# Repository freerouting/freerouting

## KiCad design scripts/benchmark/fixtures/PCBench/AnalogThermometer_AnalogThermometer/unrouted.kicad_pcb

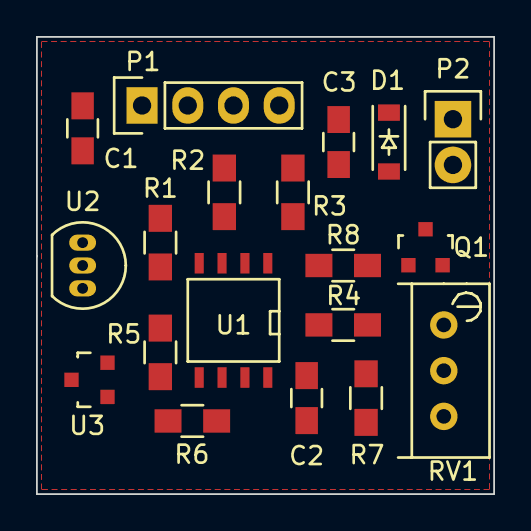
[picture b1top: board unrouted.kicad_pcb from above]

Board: 2 copper layers, 25.4 x 25.4 mm, 19 parts (0 on the bottom side), 12 nets, no tracks yet.

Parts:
C1, C2, C3: 0.1uF; C_0805_HandSoldering
D1: 1N4148; SOD-123
P1: Power; Socket_Strip_Straight_1x04
P2: uA; Socket_Strip_Straight_1x02
Q1: MMBT3904; SOT-23
R1, R4: 1M; R_0805_HandSoldering
R2, R5: 2.2M; R_0805_HandSoldering
R3, R6: 200k; R_0805_HandSoldering
R7: 49.9k; R_0805_HandSoldering
R8: 100; R_0805_HandSoldering
RV1: 100k; Potentiometer_Bourns_3296W_3-8Zoll_Inline_ScrewUp
U1: LTC1541; SOIC-8-N
U2: MCP9700A; TO-92_Inline_Narrow_Oval
U3: MCP9700AT; SOT-23

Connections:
+5V: C1.2, C2.2, C3.2, D1.1, P1.1, P2.1, U1.8, U2.1, U3.1
GND: C1.1, C2.1, P1.4, R3.1, R7.1, RV1.2, RV1.3, U1.4, U1.5, U2.3, U3.3
unnamed: C3.1, D1.2, P2.2, Q1.3
unnamed: Q1.1, R8.1
unnamed: Q1.2, R4.1, R7.2, RV1.1
unnamed: R1.1, R2.2, U1.3
unnamed: R1.2, U2.2, U3.2
unnamed: R2.1, R3.2
unnamed: R4.2, R5.2, U1.2
unnamed: R5.1, R6.2
unnamed: R6.1, U1.6
unnamed: R8.2, U1.1

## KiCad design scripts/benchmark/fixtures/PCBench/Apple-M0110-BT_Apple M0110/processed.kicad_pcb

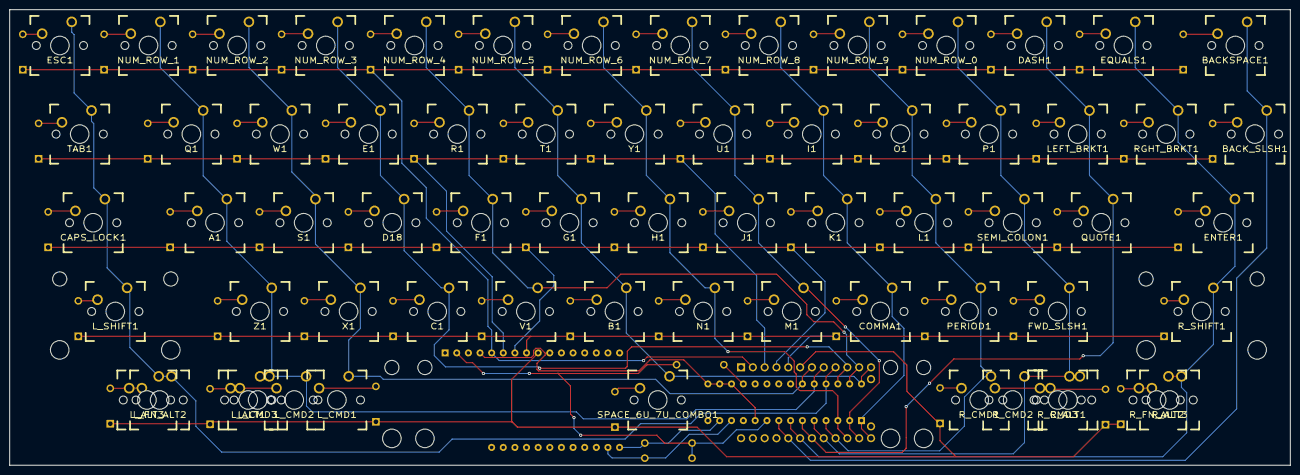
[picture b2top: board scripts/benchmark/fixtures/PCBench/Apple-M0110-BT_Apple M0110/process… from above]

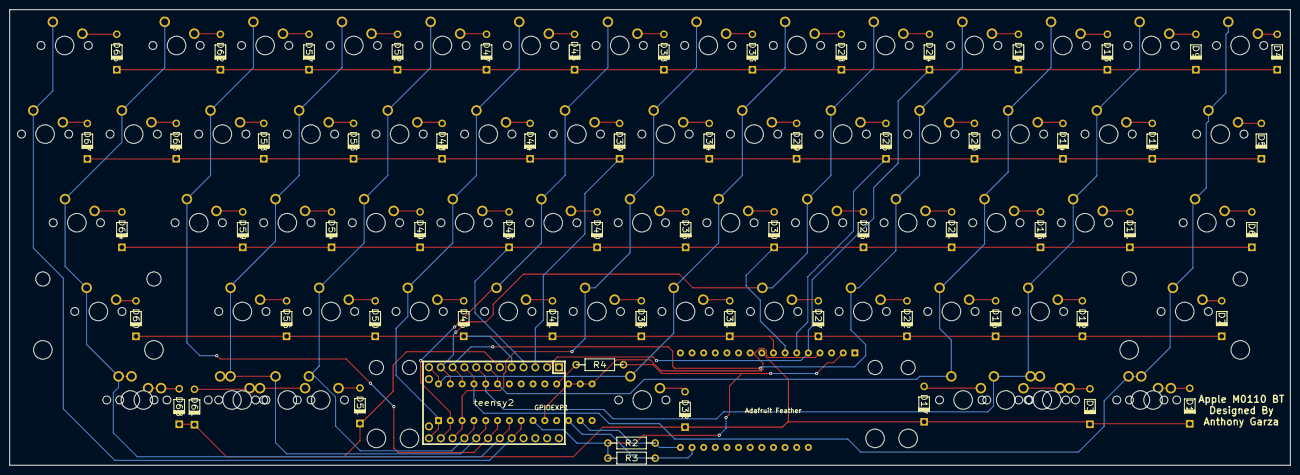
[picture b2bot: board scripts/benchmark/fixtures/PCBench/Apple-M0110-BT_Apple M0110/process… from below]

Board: 2 copper layers, 275.3 x 97.9 mm, 132 parts (66 on the bottom side), 84 nets.

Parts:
A1: SW_PUSH; MX_PCB_100H
Adafruit Feather: Adafruit_Feather; feather_32u4_bluefruit_le
B1: SW_PUSH; MX_PCB_100H
BACKSPACE1: SW_PUSH; MX_PCB_150H
BACK_SLSH1: SW_PUSH; MX_PCB_100H
C1: SW_PUSH; MX_PCB_100H
CAPS_LOCK1: SW_PUSH; MX_PCB_175H
COMMA1: SW_PUSH; MX_PCB_100H
Controller1: teensy2; Teensy_2.0
D1, D3, D4, D5, D6, D7, D9, D10, D11, D12, D13, D14, D15, D16, D17, D19, D20, D21, D22, D24, D25, D26, D27, D28, D29, D30, D31, D32, D33, D34, D35, D36, D38, D39, D40, D41, D43, D44, D45, D46, D47, D48, D49, D50, D51, D52, D53, D54, D55, D57, D58, D59, D60, D61, D62, D63, D64, D66, D67, D68: DIODE; Diode
D18: SW_PUSH; MX_PCB_100H
DASH1: SW_PUSH; MX_PCB_100H
E1: SW_PUSH; MX_PCB_100H
ENTER1: SW_PUSH; MX_PCB_175H
EQUALS1: SW_PUSH; MX_PCB_100H
ESC1: SW_PUSH; MX_PCB_100H
F1: SW_PUSH; MX_PCB_100H
FWD_SLSH1: SW_PUSH; MX_PCB_100H
G1: SW_PUSH; MX_PCB_100H
GPIOEXP1: MCP23017; MCP23017-E-SP-ND
H1: SW_PUSH; MX_PCB_100H
I1: SW_PUSH; MX_PCB_100H
J1: SW_PUSH; MX_PCB_100H
K1: SW_PUSH; MX_PCB_100H
L1: SW_PUSH; MX_PCB_100H
LEFT_BRKT1: SW_PUSH; MX_PCB_100H
L_ALT1, L_ALT3: SW_PUSH; MX_PCB_100H
L_CMD1: SW_PUSH; MX_PCB_100H
L_CMD2, L_CMD3: SW_PUSH; MX_PCB_150H
L_FN_ALT2: SW_PUSH; MX_PCB_100H
L_SHIFT1: SW_PUSH; MX_PCB_225H
M1: SW_PUSH; MX_PCB_100H
N1: SW_PUSH; MX_PCB_100H
NUM_ROW_0, NUM_ROW_1, NUM_ROW_2, NUM_ROW_3, NUM_ROW_4, NUM_ROW_5, NUM_ROW_6, NUM_ROW_7, NUM_ROW_8, NUM_ROW_9: SW_PUSH; MX_PCB_100H
O1: SW_PUSH; MX_PCB_100H
P1: SW_PUSH; MX_PCB_100H
PERIOD1: SW_PUSH; MX_PCB_100H
Q1: SW_PUSH; MX_PCB_100H
QUOTE1: SW_PUSH; MX_PCB_100H
R1: SW_PUSH; MX_PCB_100H
R2, R3, R4: R; Resistor
RGHT_BRKT1: SW_PUSH; MX_PCB_100H
R_ALT1, R_ALT3: SW_PUSH; MX_PCB_100H
R_CMD1: SW_PUSH; MX_PCB_100H
R_CMD2, R_CMD3: SW_PUSH; MX_PCB_150H
R_FN_ALT2: SW_PUSH; MX_PCB_150H
R_SHIFT1: SW_PUSH; MX_PCB_225H
S1: SW_PUSH; MX_PCB_100H
SEMI_COLON1: SW_PUSH; MX_PCB_100H
SPACE_6U_7U_COMBO1: SW_PUSH; MX_PCB_625_7_COMBO_H
T1: SW_PUSH; MX_PCB_100H
TAB1: SW_PUSH; MX_PCB_100H
U1: SW_PUSH; MX_PCB_100H
V1: SW_PUSH; MX_PCB_100H
W1: SW_PUSH; MX_PCB_100H
X1: SW_PUSH; MX_PCB_100H
Y1: SW_PUSH; MX_PCB_100H
Z1: SW_PUSH; MX_PCB_100H

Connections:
Col0: CAPS_LOCK1.1, Controller1.9, ESC1.1, GPIOEXP1.25, L_ALT3.1, L_FN_ALT2.1, L_SHIFT1.1, TAB1.1
Col1: A1.1, Controller1.8, GPIOEXP1.24, L_ALT1.1, L_CMD2.1, L_CMD3.1, NUM_ROW_1.1, Q1.1, Z1.1
Col2: Controller1.7, GPIOEXP1.23, L_CMD1.1, NUM_ROW_2.1, S1.1, W1.1, X1.1
Col3: C1.1, Controller1.10, D18.1, E1.1, GPIOEXP1.26, NUM_ROW_3.1
Col4: Controller1.11, F1.1, GPIOEXP1.27, NUM_ROW_4.1, R1.1, V1.1
Col5: B1.1, Controller1.12, G1.1, GPIOEXP1.28, NUM_ROW_5.1, SPACE_6U_7U_COMBO1.1, T1.1
Col6: Controller1.20, GPIOEXP1.3, H1.1, N1.1, NUM_ROW_6.1, Y1.1
Col7: Controller1.19, GPIOEXP1.2, J1.1, M1.1, NUM_ROW_7.1, U1.1
Col8: COMMA1.1, Controller1.18, GPIOEXP1.1, I1.1, K1.1, NUM_ROW_8.1
Col9: Controller1.21, GPIOEXP1.4, L1.1, NUM_ROW_9.1, O1.1, PERIOD1.1, R_CMD1.1
Col10: Controller1.22, FWD_SLSH1.1, GPIOEXP1.5, NUM_ROW_0.1, P1.1, R_ALT1.1, R_CMD2.1, R_CMD3.1, SEMI_COLON1.1
Col11: Controller1.23, DASH1.1, GPIOEXP1.6, LEFT_BRKT1.1, QUOTE1.1
Col12: Controller1.24, ENTER1.1, EQUALS1.1, GPIOEXP1.7, RGHT_BRKT1.1, R_ALT3.1, R_FN_ALT2.1, R_SHIFT1.1
Col13: BACKSPACE1.1, BACK_SLSH1.1, Controller1.25, GPIOEXP1.8
unnamed: A1.2, D11.1
unnamed: B1.2, D31.1
unnamed: BACKSPACE1.2, D66.1
unnamed: BACK_SLSH1.2, D67.1
unnamed: C1.2, D22.1
unnamed: Adafruit Feather.2, GPIOEXP1.9, R2.1, R3.1, R4.1
unnamed: Adafruit Feather.4, GPIOEXP1.10, GPIOEXP1.15, GPIOEXP1.16, GPIOEXP1.17
unnamed: Adafruit Feather.17, GPIOEXP1.13, R2.2
unnamed: Adafruit Feather.18, GPIOEXP1.12, R3.2
unnamed: CAPS_LOCK1.2, D6.1
unnamed: COMMA1.2, D46.1
unnamed: D1.1, L_ALT3.2, L_FN_ALT2.2
unnamed: D3.1, L_ALT1.2, L_CMD2.2, L_CMD3.2
unnamed: D4.1, ESC1.2
unnamed: D5.1, TAB1.2
unnamed: D7.1, L_SHIFT1.2
unnamed: D9.1, NUM_ROW_1.2
unnamed: D10.1, Q1.2
unnamed: D12.1, Z1.2
unnamed: D13.1, NUM_ROW_2.2
unnamed: D14.1, W1.2
unnamed: D15.1, S1.2
unnamed: D16.1, X1.2
unnamed: D17.1, L_CMD1.2
unnamed: D18.2, D21.1
unnamed: D19.1, NUM_ROW_3.2
unnamed: D20.1, E1.2
unnamed: D24.1, NUM_ROW_4.2
unnamed: D25.1, R1.2
unnamed: D26.1, F1.2
unnamed: D27.1, V1.2
unnamed: D28.1, NUM_ROW_5.2
unnamed: D29.1, T1.2
unnamed: D30.1, G1.2
unnamed: D32.1, SPACE_6U_7U_COMBO1.2
unnamed: D33.1, NUM_ROW_6.2
unnamed: D34.1, Y1.2
unnamed: D35.1, H1.2
unnamed: D36.1, N1.2
unnamed: D38.1, NUM_ROW_7.2
unnamed: D39.1, U1.2
unnamed: D40.1, J1.2
unnamed: D41.1, M1.2
unnamed: D43.1, NUM_ROW_8.2
unnamed: D44.1, I1.2
unnamed: D45.1, K1.2
unnamed: D47.1, NUM_ROW_9.2
unnamed: D48.1, O1.2
unnamed: D49.1, L1.2
unnamed: D50.1, PERIOD1.2
unnamed: D51.1, R_CMD1.2
unnamed: D52.1, NUM_ROW_0.2
unnamed: D53.1, P1.2
unnamed: D54.1, SEMI_COLON1.2
unnamed: D55.1, FWD_SLSH1.2
unnamed: D57.1, DASH1.2
unnamed: D58.1, LEFT_BRKT1.2
unnamed: D59.1, QUOTE1.2
unnamed: D60.1, R_SHIFT1.2
unnamed: D61.1, R_ALT1.2, R_CMD2.2, R_CMD3.2
unnamed: D62.1, EQUALS1.2
unnamed: D63.1, RGHT_BRKT1.2
unnamed: D64.1, ENTER1.2
unnamed: D68.1, R_ALT3.2, R_FN_ALT2.2
unnamed: GPIOEXP1.18, R4.2
Row0: Adafruit Feather.5, Controller1.2, D4.2, D9.2, D13.2, D19.2, D24.2, D28.2, D33.2, D38.2, D43.2, D47.2, D52.2, D57.2, D62.2, D66.2
Row1: Adafruit Feather.6, Controller1.3, D5.2, D10.2, D14.2, D20.2, D25.2, D29.2, D34.2, D39.2, D44.2, D48.2, D53.2, D58.2, D63.2, D67.2
Row2: Adafruit Feather.7, Controller1.4, D6.2, D11.2, D15.2, D21.2, D26.2, D30.2, D35.2, D40.2, D45.2, D49.2, D54.2, D59.2, D64.2
Row3: Adafruit Feather.8, Controller1.5, D7.2, D12.2, D16.2, D22.2, D27.2, D31.2, D36.2, D41.2, D46.2, D50.2, D55.2, D60.2
Row4: Adafruit Feather.9, Controller1.6, D1.2, D3.2, D17.2, D32.2, D51.2, D61.2, D68.2

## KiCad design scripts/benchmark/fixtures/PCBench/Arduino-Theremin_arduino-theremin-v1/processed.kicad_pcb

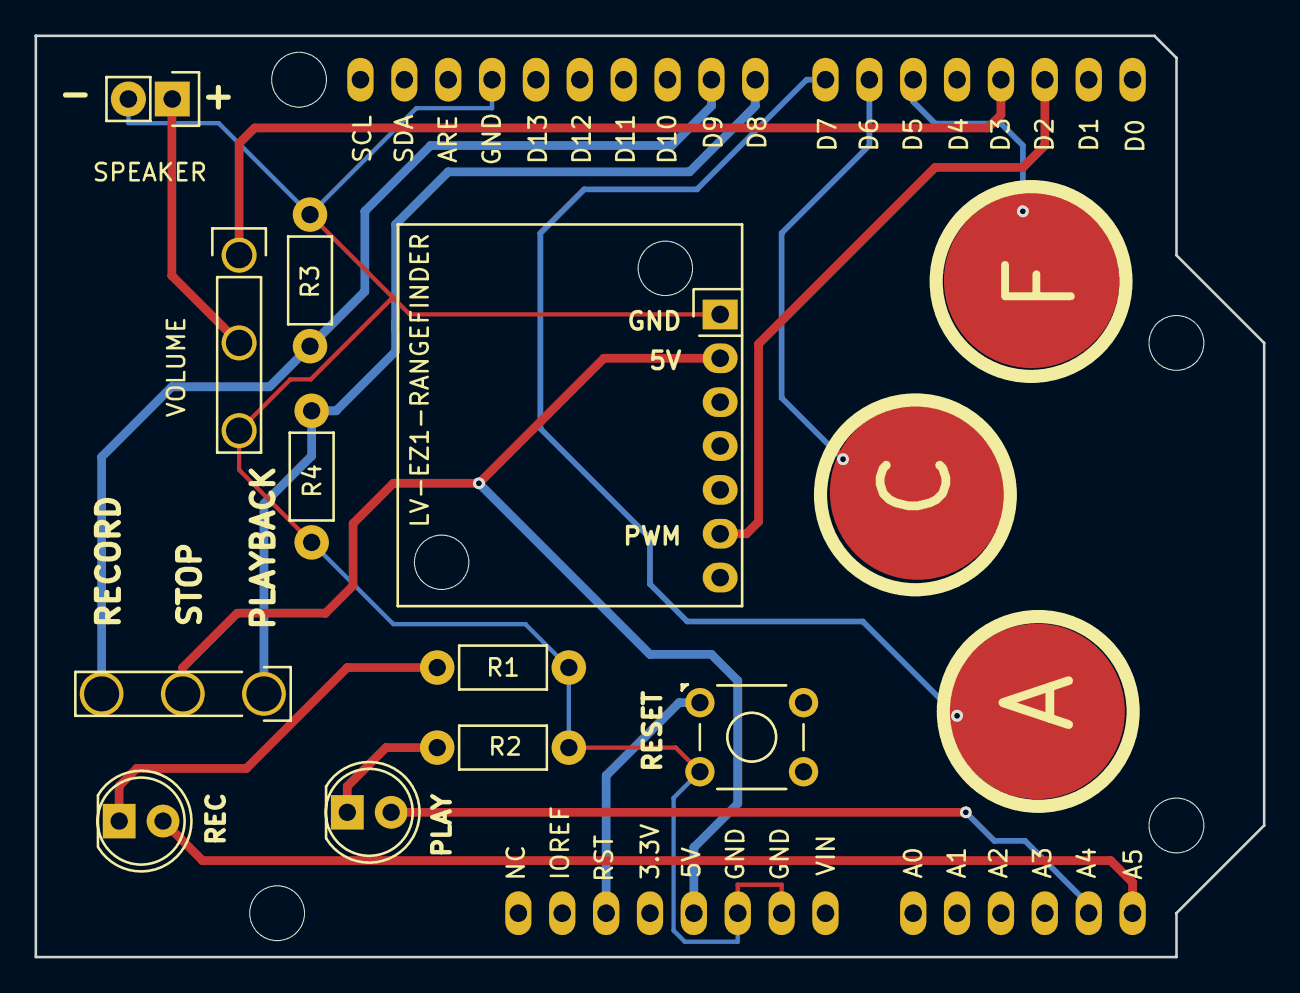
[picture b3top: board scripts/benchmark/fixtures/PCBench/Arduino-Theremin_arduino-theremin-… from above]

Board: 2 copper layers, 71.1 x 53.3 mm, 15 parts (0 on the bottom side), 15 nets.

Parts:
A: KEY1; CAPSENSE-CIRCLE-D10
C: KEY2; CAPSENSE-CIRCLE-D10
F: KEY3; CAPSENSE-CIRCLE-D10
LV-EZ1-RANGEFINDER: LV-EZ1-RANGEFINDER; LV_EZ1_Rangefinder
PLAY: PLAYBACK; LED-5MM-2PIN
R1, R2: 220; Resistor_Horizontal_RM7mm
R3, R4: 10K; Resistor_Horizontal_RM7mm
REC: RECORD; LED-5MM-2PIN
RESET: B3F-1000; SW-B3F-10XX
S1: 100SP3 ON-OFF-ON; SW-100SP3
SPEAKER: 8 OHM; OSTVN02A150
U1: ARDUINO-UNO-SHIELD; ARDU-UNOSHIELD
VOLUME: 10K; P160-TRIMPOT

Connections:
+5V: LV-EZ1-RANGEFINDER.2, S1.2, U1.5V
/A4_PLAYBACK_LED: PLAY.2, U1.A4
/A5_RECORD_LED: REC.2, U1.A5
/D2_PWM: LV-EZ1-RANGEFINDER.6, U1.D2
/D3_DIG_SPEAKER_OUT: U1.D3, VOLUME.1
/D5_KEY3: F.1, U1.D5
/D6_KEY2: C.1, U1.D6
/D7_KEY1: A.1, U1.D7
/D8_BTN_RECORD: R4.1, S1.1, U1.D8
/D9_BTN_PLAYBACK: R3.1, S1.3, U1.D9
/RESET: RESET.1, U1.RST
GND: LV-EZ1-RANGEFINDER.1, R1.2, R2.2, R3.2, R4.2, RESET.3, SPEAKER.2, U1.GND1, U1.GND2, U1.GND3, VOLUME.3
unnamed: R1.1, REC.1
unnamed: PLAY.1, R2.1
unnamed: SPEAKER.1, VOLUME.2

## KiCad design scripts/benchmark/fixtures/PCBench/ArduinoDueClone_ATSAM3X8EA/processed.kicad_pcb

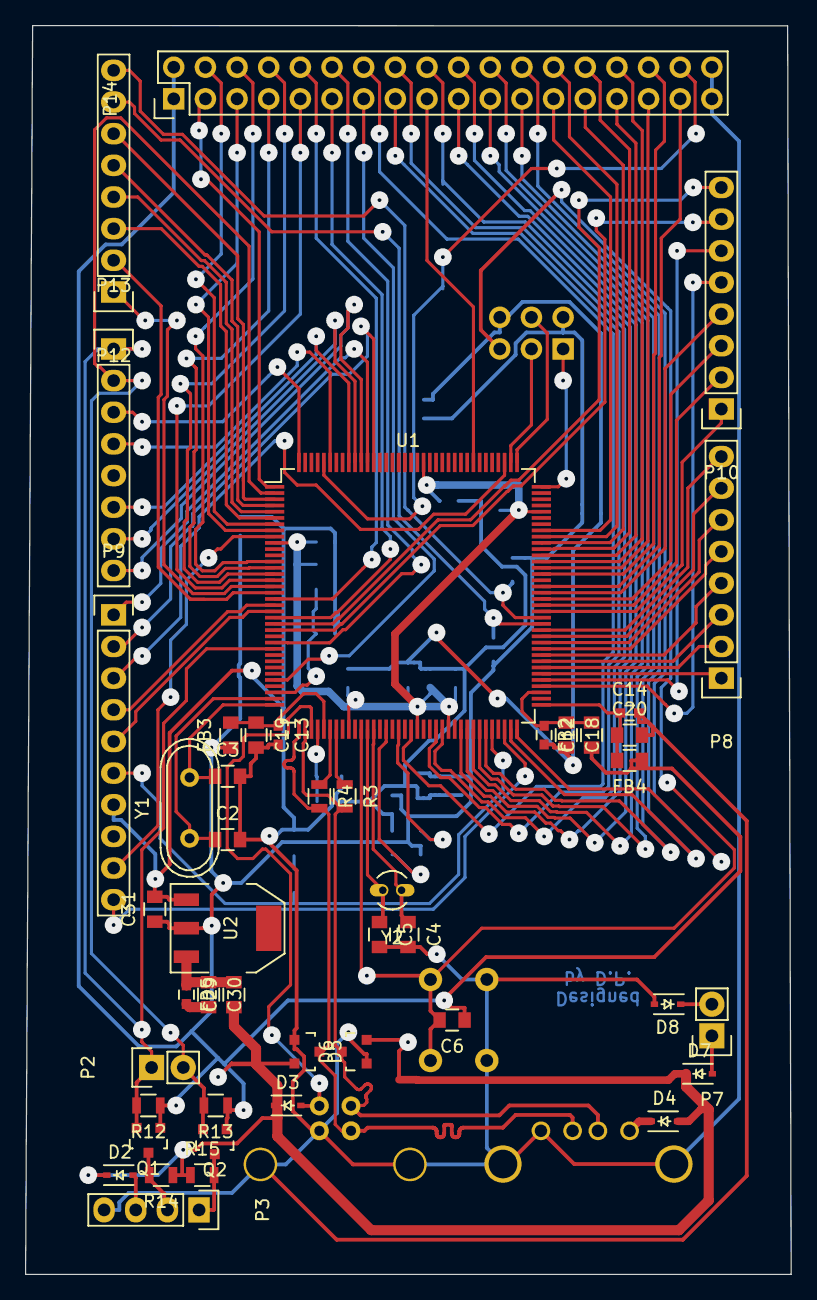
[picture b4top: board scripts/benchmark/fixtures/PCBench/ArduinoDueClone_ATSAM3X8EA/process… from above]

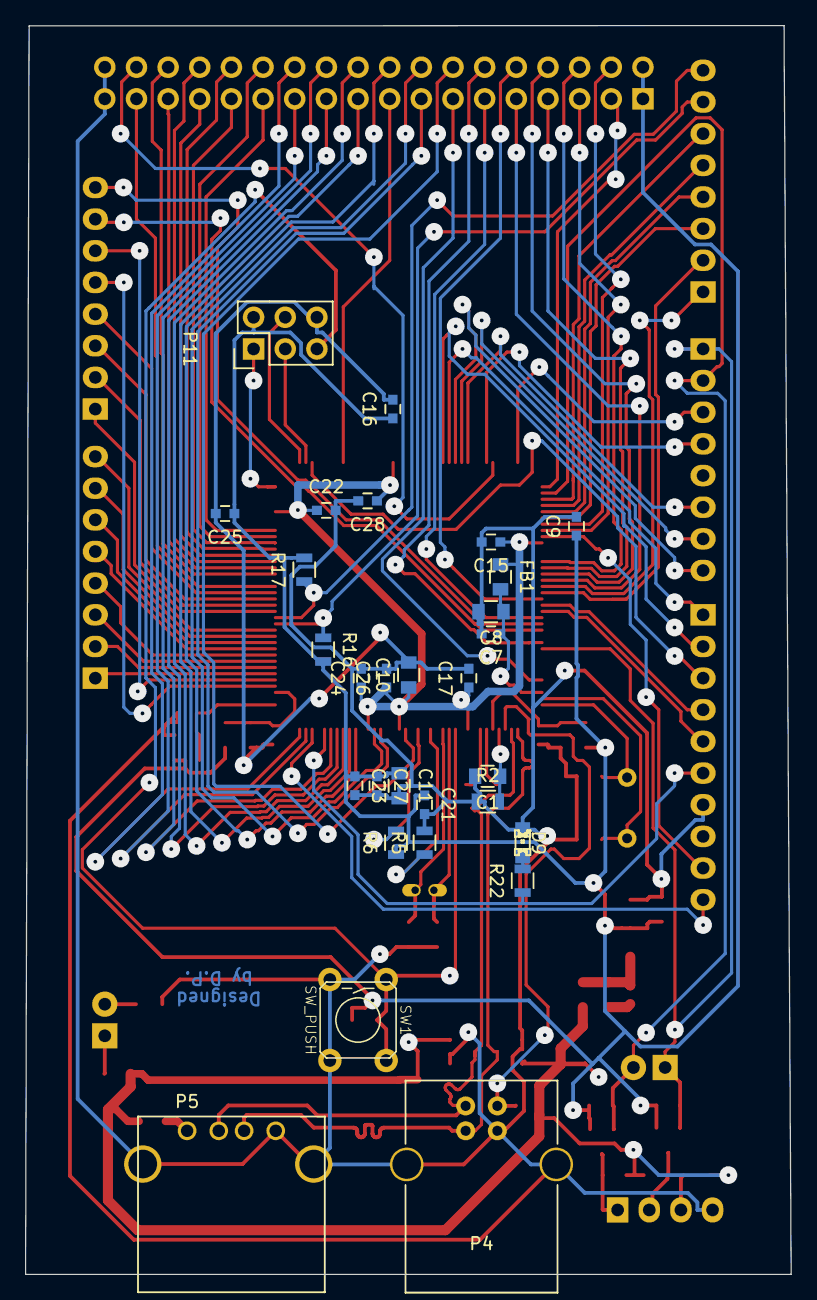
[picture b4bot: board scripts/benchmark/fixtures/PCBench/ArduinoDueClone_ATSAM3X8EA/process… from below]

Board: 2 copper layers, 61.4 x 100.2 mm, 75 parts (29 on the bottom side), 104 nets.

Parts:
C1, C2, C3, C4, C5: 22p; C_0805
C6: 10n; C_0805
C7, C9, C12, C13, C14, C15, C16, C17, C21, C22, C23, C24, C25, C26, C27, C28, C29: 100n; C_0603
C8, C10, C11, C18, C19, C20, C30, C31: 10u; C_0805
D2, D3, D4, D7, D8: PMEG2010AEH; SOD-323
D5, D6: BAV99; SOT-23
D9: LED; LED-0805
FB1, FB2, FB3, FB4, FB5: MH2029-300Y; C_0805
P2: 3.3V Serial; Pin_Header_Straight_1x02
P3: 5V_Serial; Pin_Header_Straight_1x04
P4: USB_B
P5: USB_A
P7: 5V_Power; Pin_Header_Straight_1x02
P8: ADCL; Pin_Header_Straight_1x08
P9: PWMH; Pin_Header_Straight_1x10
P10: ADCH; Pin_Header_Straight_1x08
P11: SPI; Pin_Header_Straight_2x03
P12: Communication; Pin_Header_Straight_1x08
P13: PWML; Pin_Header_Straight_1x08
P14: CONN_02X18; Pin_Header_Straight_2x18
Q1, Q2: BSS138; SOT-23
R2: 6k8 1%; R_0805
R3, R4: 39R 1%; R_0805
R5: NC; R_0805
R6: 100k; R_0805
R12, R13, R14, R15: 10k; R_0805
R16, R17: 1k5; R_0805
R22: 330; R_0805
SW1: SW_PUSH; 6MM_PushButton
U1: ATSAM3X8EA-AU; LQFP-144_20x20mm_Pitch0.5mm
U2: LD1117S33TR; SOT-223
Y1: 12MHz; Crystal_HC49-U_Vertical
Y2: 32.768Khz; Crystal_Round_Vertical_3mm_BigPad

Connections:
3.3V: C6.1, C9.1, C11.1, C16.1, C21.1, C23.1, C25.1, C27.1, C31.1, FB2.1, FB3.1, FB4.1, P11.2, P14.1, P14.2, Q1.1, Q2.1, R6.1, R12.1, R13.1, R16.2, R17.2, U2.2
/ATSAM3X8EA-AU/ADCREF: C12.1, C18.1, FB2.2, U1.75
/ATSAM3X8EA-AU/D+: D5.3, P4.3, P5.3, R4.2, U1.37
/ATSAM3X8EA-AU/D-: D6.3, P4.2, P5.2, R3.2, U1.38
/ATSAM3X8EA-AU/HSD+: R4.1, U1.42
/ATSAM3X8EA-AU/HSD-: R3.1, U1.43
/ATSAM3X8EA-AU/PA0: P10.8, U1.23
/ATSAM3X8EA-AU/PA1: P10.7, U1.24
/ATSAM3X8EA-AU/PA2: P8.8, U1.85
/ATSAM3X8EA-AU/PA3: P8.7, U1.84
/ATSAM3X8EA-AU/PA4: P8.6, U1.83
/ATSAM3X8EA-AU/PA6: P8.5, U1.82
/ATSAM3X8EA-AU/PA7: P14.12, U1.26
/ATSAM3X8EA-AU/PA10: P12.6, U1.3
/ATSAM3X8EA-AU/PA11: P12.5, U1.4
/ATSAM3X8EA-AU/PA12: P12.4, U1.5
/ATSAM3X8EA-AU/PA13: P12.3, U1.6
/ATSAM3X8EA-AU/PA14: P14.4, U1.7
/ATSAM3X8EA-AU/PA15: P14.5, U1.8
/ATSAM3X8EA-AU/PA16: P8.1, U1.78
/ATSAM3X8EA-AU/PA17: P9.9, U1.9
/ATSAM3X8EA-AU/PA18: P9.10, U1.70
/ATSAM3X8EA-AU/PA19: P14.23, U1.71
/ATSAM3X8EA-AU/PA20: P14.24, U1.72
/ATSAM3X8EA-AU/PA22: P8.4, U1.81
/ATSAM3X8EA-AU/PA23: P8.3, U1.80
/ATSAM3X8EA-AU/PA24: P8.2, U1.79
/ATSAM3X8EA-AU/PA25: P11.1, U1.108
/ATSAM3X8EA-AU/PA26: P11.4, U1.109
/ATSAM3X8EA-AU/PA27: P11.3, U1.110
/ATSAM3X8EA-AU/PA28: P9.3, U1.111
/ATSAM3X8EA-AU/PB12: P12.7, R16.1, U1.86
/ATSAM3X8EA-AU/PB13: P12.8, R17.1, U1.87
/ATSAM3X8EA-AU/PB14: P14.34, U1.140
/ATSAM3X8EA-AU/PB15: P10.5, U1.76
/ATSAM3X8EA-AU/PB16: P10.6, U1.77
/ATSAM3X8EA-AU/PB17: P10.1, U1.88
/ATSAM3X8EA-AU/PB18: P10.2, U1.89
/ATSAM3X8EA-AU/PB19: P10.3, U1.90
/ATSAM3X8EA-AU/PB20: P10.4, U1.91
/ATSAM3X8EA-AU/PB21: P14.33, U1.92
/ATSAM3X8EA-AU/PB25: P13.3, U1.144
/ATSAM3X8EA-AU/PB26: P14.3, U1.1
/ATSAM3X8EA-AU/PB27: P9.6, R22.1, U1.68
/ATSAM3X8EA-AU/PC1: P14.14, U1.55
/ATSAM3X8EA-AU/PC2: P14.15, U1.59
/ATSAM3X8EA-AU/PC3: P14.16, U1.60
/ATSAM3X8EA-AU/PC4: P14.17, U1.116
/ATSAM3X8EA-AU/PC5: P14.18, U1.63
/ATSAM3X8EA-AU/PC6: P14.19, U1.64
/ATSAM3X8EA-AU/PC7: P14.20, U1.65
/ATSAM3X8EA-AU/PC8: P14.21, U1.66
/ATSAM3X8EA-AU/PC9: P14.22, U1.67
/ATSAM3X8EA-AU/PC12: P14.32, U1.94
/ATSAM3X8EA-AU/PC13: P14.31, U1.95
/ATSAM3X8EA-AU/PC14: P14.30, U1.96
/ATSAM3X8EA-AU/PC15: P14.29, U1.97
/ATSAM3X8EA-AU/PC16: P14.28, U1.98
/ATSAM3X8EA-AU/PC17: P14.27, U1.99
/ATSAM3X8EA-AU/PC18: P14.26, U1.100
/ATSAM3X8EA-AU/PC19: P14.25, U1.101
/ATSAM3X8EA-AU/PC21: P9.2, U1.132
/ATSAM3X8EA-AU/PC22: P9.1, U1.133
/ATSAM3X8EA-AU/PC23: P13.8, U1.134
/ATSAM3X8EA-AU/PC24: P13.7, U1.135
/ATSAM3X8EA-AU/PC25: P13.6, U1.136
/ATSAM3X8EA-AU/PC28: P13.4, U1.139
/ATSAM3X8EA-AU/PD0: P14.6, U1.13
/ATSAM3X8EA-AU/PD1: P14.7, U1.14
/ATSAM3X8EA-AU/PD2: P14.8, U1.15
/ATSAM3X8EA-AU/PD3: P14.9, U1.16
/ATSAM3X8EA-AU/PD4: P12.1, U1.17
/ATSAM3X8EA-AU/PD5: P12.2, U1.18
/ATSAM3X8EA-AU/PD6: P14.10, U1.19
/ATSAM3X8EA-AU/PD7: P9.4, U1.20
/ATSAM3X8EA-AU/PD8: P9.5, U1.21
/ATSAM3X8EA-AU/PD9: P14.11, U1.22
/ATSAM3X8EA-AU/PD10: P14.13, U1.32
/ATSAM3X8EA-AU/RX: P2.1, P13.1, Q1.2, R12.2, U1.27
/ATSAM3X8EA-AU/TX: P2.2, P13.2, Q2.2, R13.2, U1.2
/ATSAM3X8EA-AU/VBUS: D3.2, P4.1, U1.39
/ATSAM3X8EA-AU/VDDANA: C14.1, C20.1, FB4.2, U1.73
/ATSAM3X8EA-AU/VDDOUT: C10.1, C15.1, C17.1, C22.1, C24.1, C26.1, C28.1, FB1.1, U1.10, U1.45, U1.56, U1.61, U1.104, U1.124
/ATSAM3X8EA-AU/VDDOUTMI: C13.1, C19.1, FB3.2, U1.41
/Connections/MASTER_RESET: C6.2, P11.5, SW1.1, U1.47
/Power/5V: D2.1, D3.1, D4.2, D5.2, D6.2, D7.1, FB5.1, R14.1, R15.1
/Serial/RX_5V: P3.2, Q1.3, R14.2
/Serial/TX_5V: P3.1, Q2.3, R15.2
/Serial/VCC_SERIAL: D2.2, P3.3
GND: C1.2, C2.2, C3.2, C4.2, C5.2, C7.2, C8.2, C9.2, C10.2, C11.2, C12.2, C13.2, C14.2, C15.2, C16.2, C17.2, C18.2, C19.2, C20.2, C21.2, C22.2, C23.2, C24.2, C25.2, C26.2, C27.2, C28.2, C31.2, D5.1, D6.1, D8.2, D9.1, P3.4, P4.4, P4.5, P5.4, P5.5, P9.7, P11.6, P14.35, P14.36, R2.1, R5.2, SW1.2, U2.1
unnamed: C1.1, R2.2, U1.40
unnamed: C2.1, U1.35, Y1.1
unnamed: C3.1, U1.36, Y1.2
unnamed: C4.1, U1.49, Y2.1
unnamed: C5.1, U1.48, Y2.2
unnamed: C7.1, C8.1, FB1.2, U1.34
unnamed: C29.1, C30.1, FB5.2, U2.3
unnamed: C29.2, C30.2
unnamed: D4.1, P5.1
unnamed: D7.2, P7.1
unnamed: D8.1, P7.2
unnamed: D9.2, R22.2
unnamed: R5.1, U1.51
unnamed: R6.2, U1.53

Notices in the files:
scripts/benchmark/fixtures/PCBench/Arduino-Theremin_arduino-theremin-v1/processed.kicad_pcb:
Released under the CERN Open Hardware License v1.2
